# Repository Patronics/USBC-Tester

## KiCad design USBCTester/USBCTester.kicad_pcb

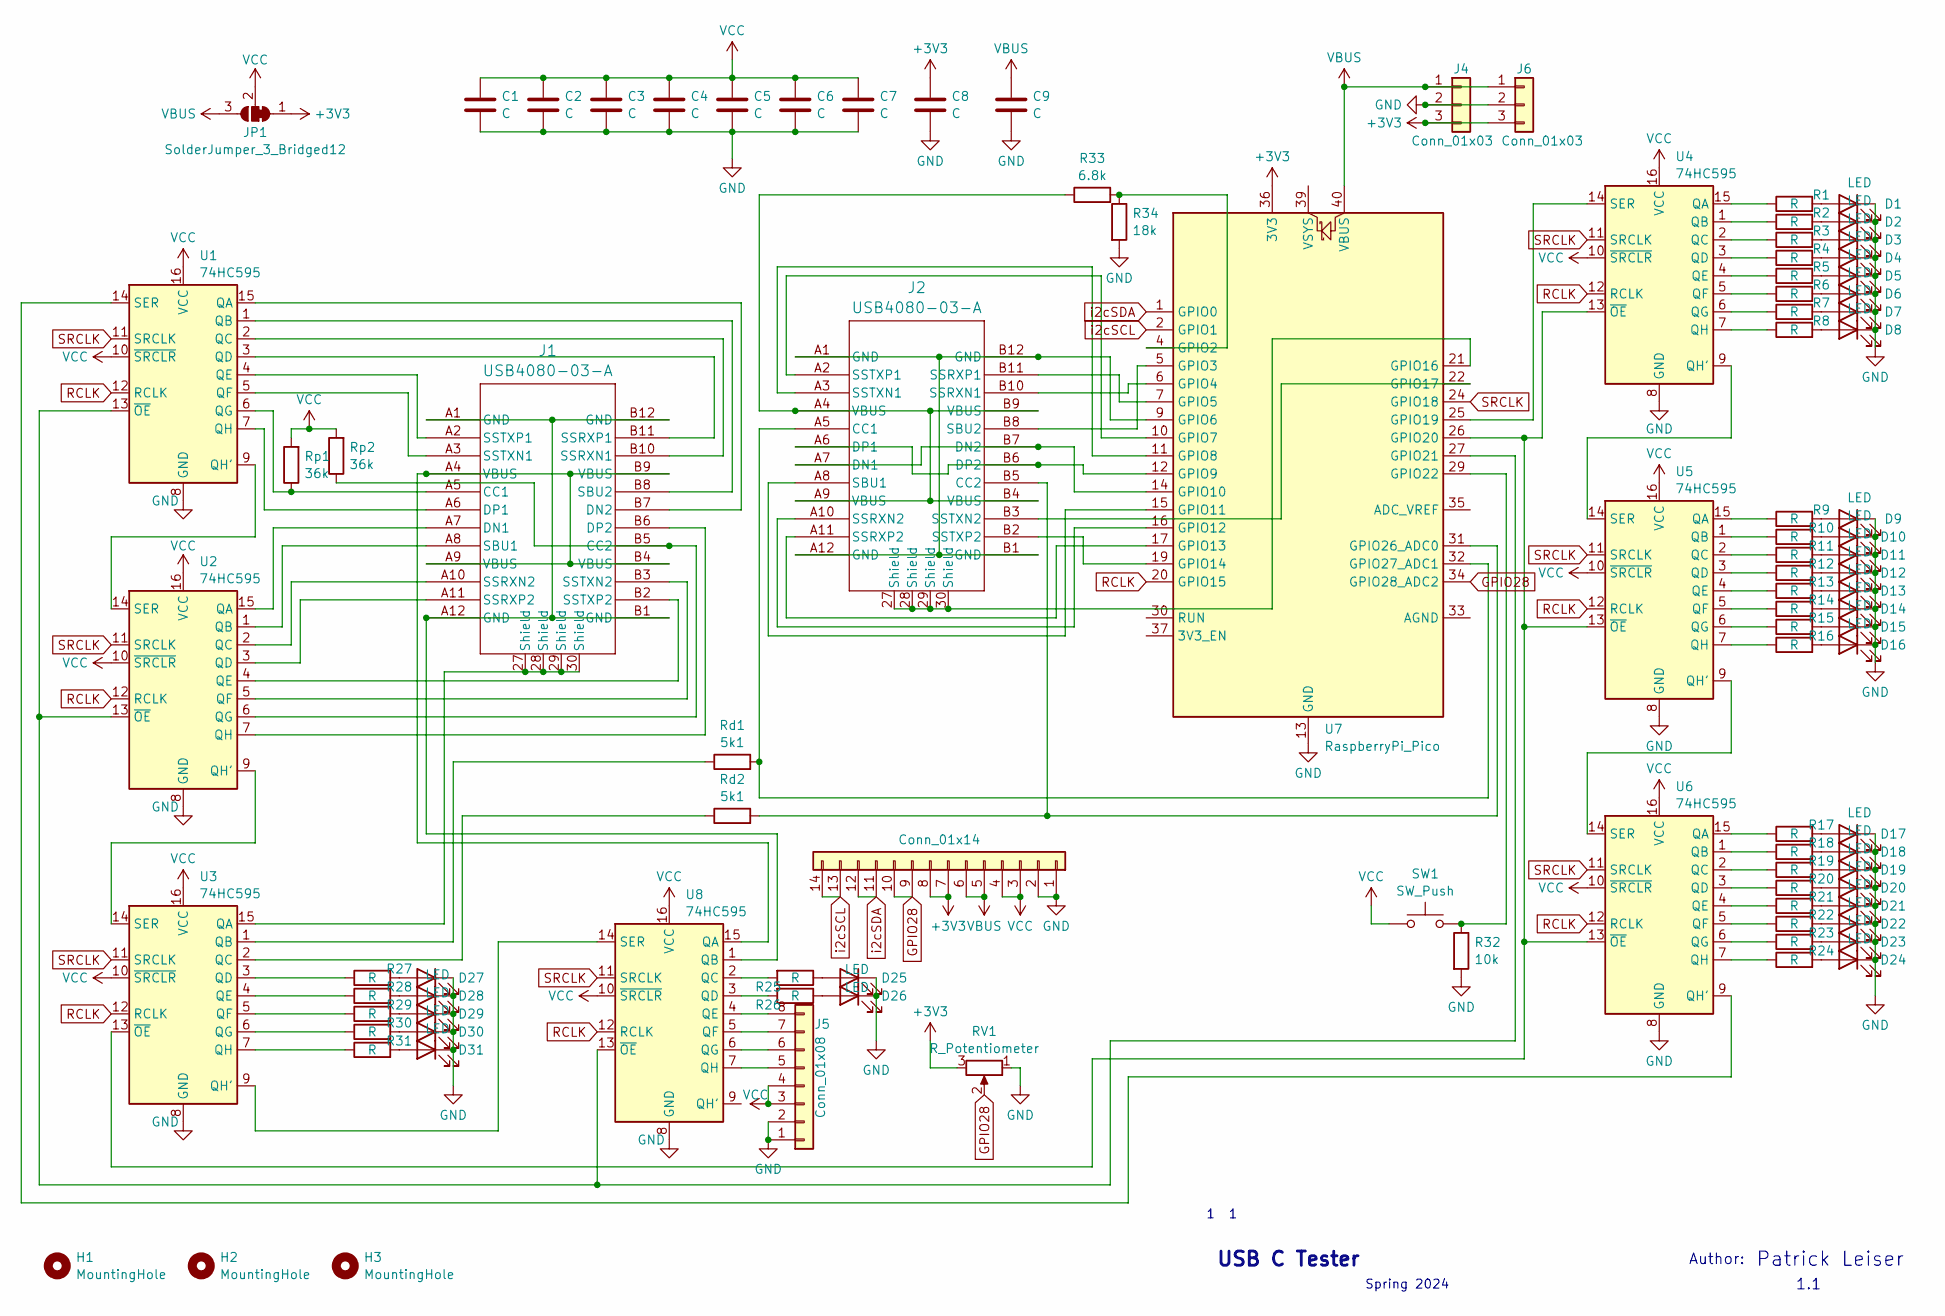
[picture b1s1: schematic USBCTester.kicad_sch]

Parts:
C1, C2, C3, C4, C5, C6, C7, C8, C9: C; C_0603_1608Metric
D1, D2, D3, D4, D5, D6, D7, D8, D9, D10, D11, D12, D13, D14, D15, D16, D17, D18, D19, D20, D21, D22, D23, D24, D25, D26, D27, D28, D29, D30, D31: LED; LED_0603_1608Metric
H1, H2, H3: MountingHole; MountingHole_3.2mm_M3
J1, J2: USB4080-03-A; USB4080-03-A_GCT_RoundHoles
J3: Conn_01x14; PinSocket_1x14_P2.54mm_Vertical
J4, J6: Conn_01x03; PinSocket_1x03_P2.54mm_Vertical
J5: Conn_01x08; PinHeader_2x04_P2.54mm_Vertical
JP1: SolderJumper_3_Bridged12; SolderJumper-3_P1.3mm_Bridged12_RoundedPad1.0x1.5mm
R1, R2, R3, R4, R5, R6, R7, R8, R9, R10, R11, R12, R13, R14, R15, R16, R17, R18, R19, R20, R21, R22, R23, R24, R25, R26, R27, R28, R29, R30, R31: R; R_0603_1608Metric
R32: 10k; R_0603_1608Metric
R33: 6.8k; R_0603_1608Metric
R34: 18k; R_0603_1608Metric
RV1: R_Potentiometer; TRIM_35WR10KLFTR
Rd1, Rd2: 5k1; R_0603_1608Metric
Rp1, Rp2: 36k; R_0603_1608Metric
SW1: SW_Push; SW_Push_1P1T_NO_6x6mm_H9.5mm
U1, U2, U3, U4, U5, U6, U8: 74HC595; SOIC-16_3.9x9.9mm_P1.27mm
U7: RaspberryPi_Pico; RaspberryPi_Pico_Common

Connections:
+3V3: C8.1, J3.7, J3.8, J4.3, J6.3, JP1.1 (A), RV1.3, U7.36 (3V3)
GND: C1.2, C2.2, C3.2, C4.2, C5.2, C6.2, C7.2, C8.2, C9.2, D1.1 (K), D2.1 (K), D3.1 (K), D4.1 (K), D5.1 (K), D6.1 (K), D7.1 (K), D8.1 (K), D9.1 (K), D10.1 (K), D11.1 (K), D12.1 (K), D13.1 (K), D14.1 (K), D15.1 (K), D16.1 (K), D17.1 (K), D18.1 (K), D19.1 (K), D20.1 (K), D21.1 (K), D22.1 (K), D23.1 (K), D24.1 (K), D25.1 (K), D26.1 (K), D27.1 (K), D28.1 (K), D29.1 (K), D30.1 (K), D31.1 (K), J3.1, J3.2, J4.2, J5.1, J5.2, J6.2, R32.2, R34.2, RV1.1, U1.8 (GND), U2.8 (GND), U3.8 (GND), U4.8 (GND), U5.8 (GND), U6.8 (GND), U7.3 (GND), U7.8 (GND), U7.13 (GND), U7.18 (GND), U7.23 (GND), U7.28 (GND), U7.38 (GND), U8.8 (GND)
GPIO28: J3.9, J3.10, RV1.2, U7.34 (GPIO28_ADC2)
unnamed: D1.2 (A), R1.2
unnamed: D2.2 (A), R2.2
unnamed: D3.2 (A), R3.2
unnamed: D4.2 (A), R4.2
unnamed: D5.2 (A), R5.2
unnamed: D6.2 (A), R6.2
unnamed: D7.2 (A), R7.2
unnamed: D8.2 (A), R8.2
unnamed: D9.2 (A), R9.2
unnamed: D10.2 (A), R10.2
unnamed: D11.2 (A), R11.2
unnamed: D12.2 (A), R12.2
unnamed: D13.2 (A), R13.2
unnamed: D14.2 (A), R14.2
unnamed: D15.2 (A), R15.2
unnamed: D16.2 (A), R16.2
unnamed: D17.2 (A), R17.2
unnamed: D18.2 (A), R18.2
unnamed: D19.2 (A), R19.2
unnamed: D20.2 (A), R20.2
unnamed: D21.2 (A), R21.2
unnamed: D22.2 (A), R22.2
unnamed: D23.2 (A), R23.2
unnamed: D24.2 (A), R24.2
unnamed: D25.2 (A), R25.1
unnamed: D26.2 (A), R26.1
unnamed: D27.2 (A), R27.2
unnamed: D28.2 (A), R28.2
unnamed: D29.2 (A), R29.2
unnamed: D30.2 (A), R30.2
unnamed: D31.2 (A), R31.2
unnamed: J1.A5 (CC1), Rp1.1, U1.6 (QG)
unnamed: J1.B5 (CC2), Rp2.1, U2.6 (QG)
unnamed: J1.A7 (DN1), U2.15 (QA)
unnamed: J1.B7 (DN2), U1.15 (QA)
unnamed: J1.A6 (DP1), U1.7 (QH)
unnamed: J1.B6 (DP2), U2.7 (QH)
unnamed: J1.A8 (SBU1), U2.1 (QB)
unnamed: J1.B8 (SBU2), U1.1 (QB)
unnamed: J1.B10 (SSRXN1), U1.2 (QC)
unnamed: J1.A10 (SSRXN2), U2.2 (QC)
unnamed: J1.B11 (SSRXP1), U1.3 (QD)
unnamed: J1.A11 (SSRXP2), U2.3 (QD)
unnamed: J1.A3 (SSTXN1), U1.5 (QF)
unnamed: J1.B3 (SSTXN2), U2.5 (QF)
unnamed: J1.A2 (SSTXP1), U1.4 (QE)
unnamed: J1.B2 (SSTXP2), U2.4 (QE)
unnamed: J2.A5 (CC1), Rd1.2, U7.32 (GPIO27_ADC1)
unnamed: J2.B5 (CC2), Rd2.2, U7.31 (GPIO26_ADC0)
unnamed: J2.A7 (DN1), J2.B7 (DN2), U7.14 (GPIO10)
unnamed: J2.A6 (DP1), J2.B6 (DP2), U7.12 (GPIO9)
unnamed: J2.A8 (SBU1), U7.15 (GPIO11)
unnamed: J2.B8 (SBU2), U7.5 (GPIO3)
unnamed: J2.B10 (SSRXN1), U7.6 (GPIO4)
unnamed: J2.A10 (SSRXN2), U7.16 (GPIO12)
unnamed: J2.B11 (SSRXP1), U7.7 (GPIO5)
unnamed: J2.A11 (SSRXP2), U7.17 (GPIO13)
unnamed: J2.A3 (SSTXN1), U7.11 (GPIO8)
unnamed: J2.B3 (SSTXN2), U7.22 (GPIO17)
unnamed: J2.A2 (SSTXP1), U7.10 (GPIO7)
unnamed: J2.B2 (SSTXP2), U7.19 (GPIO14)
unnamed: J2.A4 (VBUS), J2.A9 (VBUS), J2.B4 (VBUS), J2.B9 (VBUS), R33.1
unnamed: J5.5, U8.7 (QH)
unnamed: J5.6, U8.6 (QG)
unnamed: J5.7, U8.5 (QF)
unnamed: J5.8, U8.4 (QE)
unnamed: U1.9 (QH'), U2.14 (SER)
unnamed: U1.14 (SER), U6.9 (QH')
unnamed: U1.13 (~OE), U2.13 (~OE), U7.27 (GPIO21), U8.13 (~OE)
unnamed: U2.9 (QH'), U3.14 (SER)
unnamed: J1.27 (Shield), J1.28 (Shield), J1.29 (Shield), J1.30 (Shield), U3.15 (QA)
unnamed: Rd1.1, U3.1 (QB)
unnamed: Rd2.1, U3.2 (QC)
unnamed: R27.1, U3.3 (QD)
unnamed: R28.1, U3.4 (QE)
unnamed: R29.1, U3.5 (QF)
unnamed: R30.1, U3.6 (QG)
unnamed: U3.9 (QH'), U8.14 (SER)
unnamed: R31.1, U3.7 (QH)
unnamed: U3.13 (~OE), U4.13 (~OE), U5.13 (~OE), U6.13 (~OE), U7.26 (GPIO20)
unnamed: R1.1, U4.15 (QA)
unnamed: R2.1, U4.1 (QB)
unnamed: R3.1, U4.2 (QC)
unnamed: R4.1, U4.3 (QD)
unnamed: R5.1, U4.4 (QE)
unnamed: R6.1, U4.5 (QF)
unnamed: R7.1, U4.6 (QG)
unnamed: U4.9 (QH'), U5.14 (SER)
unnamed: R8.1, U4.7 (QH)
unnamed: U4.14 (SER), U7.25 (GPIO19)
unnamed: R9.1, U5.15 (QA)
unnamed: R10.1, U5.1 (QB)
unnamed: R11.1, U5.2 (QC)
unnamed: R12.1, U5.3 (QD)
unnamed: R13.1, U5.4 (QE)
unnamed: R14.1, U5.5 (QF)
unnamed: R15.1, U5.6 (QG)
unnamed: U5.9 (QH'), U6.14 (SER)
unnamed: R16.1, U5.7 (QH)
unnamed: R17.1, U6.15 (QA)
unnamed: R18.1, U6.1 (QB)
unnamed: R19.1, U6.2 (QC)
unnamed: R20.1, U6.3 (QD)
unnamed: R21.1, U6.4 (QE)
unnamed: R22.1, U6.5 (QF)
unnamed: R23.1, U6.6 (QG)
unnamed: R24.1, U6.7 (QH)
unnamed: R33.2, R34.1, U7.4 (GPIO2)
unnamed: J2.A1 (GND), J2.A12 (GND), J2.B1 (GND), J2.B12 (GND), U7.9 (GPIO6)
unnamed: J2.27 (Shield), J2.28 (Shield), J2.29 (Shield), J2.30 (Shield), U7.21 (GPIO16)
unnamed: R32.1, SW1.2, U7.29 (GPIO22)
unnamed: J1.A4 (VBUS), J1.A9 (VBUS), J1.B4 (VBUS), J1.B9 (VBUS), U8.15 (QA)
unnamed: J1.A1 (GND), J1.A12 (GND), J1.B1 (GND), J1.B12 (GND), U8.1 (QB)
unnamed: R25.2, U8.2 (QC)
unnamed: R26.2, U8.3 (QD)
RCLK: U1.12 (RCLK), U2.12 (RCLK), U3.12 (RCLK), U4.12 (RCLK), U5.12 (RCLK), U6.12 (RCLK), U7.20 (GPIO15), U8.12 (RCLK)
SRCLK: U1.11 (SRCLK), U2.11 (SRCLK), U3.11 (SRCLK), U4.11 (SRCLK), U5.11 (SRCLK), U6.11 (SRCLK), U7.24 (GPIO18), U8.11 (SRCLK)
VBUS: C9.1, J3.5, J3.6, J4.1, J6.1, JP1.3 (B), U7.40 (VBUS)
VCC: C1.1, C2.1, C3.1, C4.1, C5.1, C6.1, C7.1, J3.3, J3.4, J5.3, J5.4, JP1.2 (C), Rp1.2, Rp2.2, SW1.1, U1.10 (~SRCLR), U1.16 (VCC), U2.10 (~SRCLR), U2.16 (VCC), U3.10 (~SRCLR), U3.16 (VCC), U4.10 (~SRCLR), U4.16 (VCC), U5.10 (~SRCLR), U5.16 (VCC), U6.10 (~SRCLR), U6.16 (VCC), U8.10 (~SRCLR), U8.16 (VCC)
i2cSCL: J3.13, J3.14, U7.2 (GPIO1)
i2cSDA: J3.11, J3.12, U7.1 (GPIO0)

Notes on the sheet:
Author:
Spring 2024
Patrick Leiser
1.1
1 1
USB C Tester

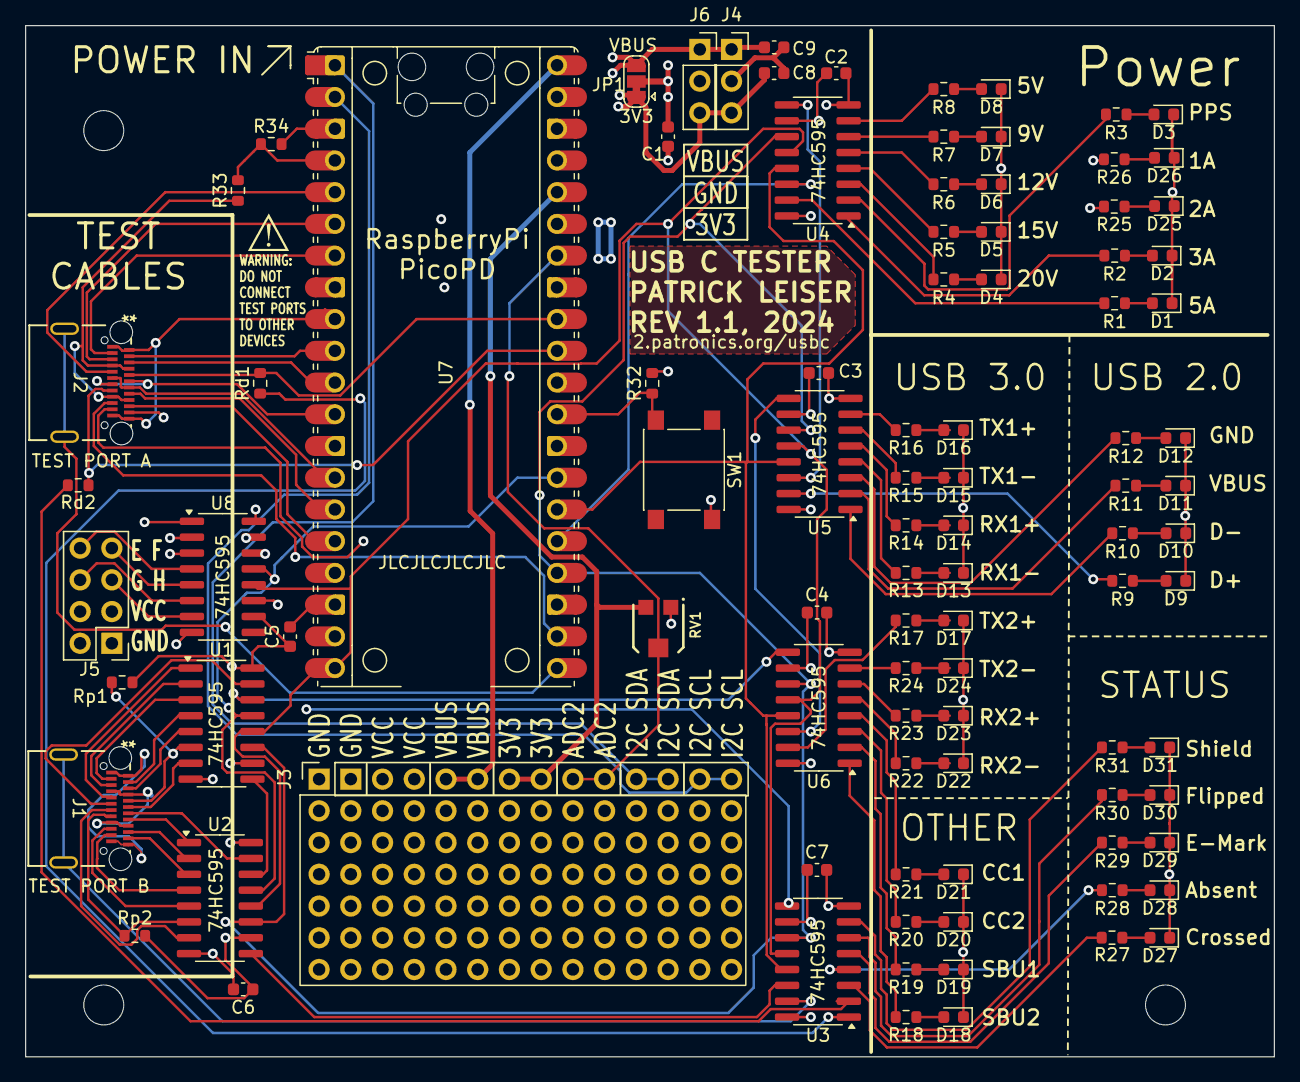
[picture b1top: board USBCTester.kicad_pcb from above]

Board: 4 copper layers, 100.0 x 82.6 mm, 99 parts (0 on the bottom side), 124 nets.

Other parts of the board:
PB1: ProtoBoard 14x6

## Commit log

2024-02-11 initial commit, add kicad files so far
2024-02-11 add power plane and vias for high current and decoupling caps
2024-02-12 continu wiring and add decoupling caps
2024-02-12 add usb c port footprint and symbol
2024-02-12 organize usb2 and usb3 status leds
2024-02-13 add more leds and route almost everything
2024-02-13 label all LEDs
2024-02-13 add breakout pins for prototyping
2024-02-16 made board more compact
2024-02-16 add 3rd incompatible footprint design
2024-02-16 switch to USB4080 footprint
2024-02-16 add protoboard, lots of tweaks and silkscreen improvements
2024-02-21 many tweaks to finalize design, then Schematic update for safety with external devices
2024-02-21 update layout with improved external device safety and testing for active cables
2024-02-26 pretty and useful back silkscreen
2024-02-27 adjust layout to preseve i2c pins, and general layout cleanup
2024-02-27 minor cleanup and reorganization
2024-02-27 adjust text background style, last 7.0 commit
2024-02-29 use older footprint for USBC since JLCPCB does seem to tolerate the shape, and minor silkscreen fixes
2024-03-04 simplify nested folders
2024-03-04 add basic openocd config file for programming via debugger
2024-03-04 move pretty footprints
2024-03-10 initial commit of power tester, proof of concept drives shift registers
2024-03-10 implemented functions for setting precice output from shift registers
2024-03-10 make remapLeds function to set LED bitmap to cleaner order
2024-03-10 minor fix and optimization
2024-03-10 successfully tests USB PD voltages
2024-03-10 animate progress in scanning supported voltages
2024-03-10 improve handling of tolerances, especially 5v tolerance
2024-03-10 rename shiftOut to shiftOutBit to avoid overriding Arduino's native shiftOut function
2024-03-11 add defines for all the pico's pins
2024-03-12 add checkPinConnection function and many #defines for pins
2024-03-12 test shield connection
2024-03-12 add software dimming of bright leds
2024-03-12 add ifdef to disable pwm dimming if not needed
2024-03-13 add errata notes
2024-03-19 update kicad files with JLC BOM and to fix silkscreen issue in V1
2024-03-19 add errata description of individual boards
2024-03-19 add #defines for each physical board made so far for hardware-specific tweaks as needed
2024-03-24 add comment noting idea for scanning brightness of power LEDs to indicate current level per supported voltage
2024-03-30 improve handling of shift registers without output enable pins
2024-03-30 add errataboard 4
2024-03-30 fine-tune timing for shift register shields
2024-03-30 WIP improve handling of shield (internally tied to ground), and start on testing other pins badly
2024-04-25 revision 1.2, add another shift register and fix the production files
2024-04-25 add resistors to db
2024-04-30 update errata to handle board rev 1.1. Final version of code optimized for v1.0 boards
2024-04-30 semi-untested modifications for rev1.1 boards
2024-04-30 fixed infinite loop due to inadequate type sizes
2024-05-01 lots of progress on getCurrentLEDsForVoltage
2024-05-03 complete getCurrentForVoltage function
2024-05-03 add tracking and displaying semantic versioning info at boot
2024-05-03 all pins defined
2024-05-03 successfully tests USB2 data+ pin
2024-05-03 testing most pins works, including D+/D-, SBU1/SBU2, and the SS pins(untested)
2024-05-03 fix handling of USB3 pins
2024-05-03 Fix power pins, shield, and re-add absent indicator
2024-05-06 add descriptive comments for CC pins
2024-05-09 slow down sampling in order to make kendrick's cable vbus work
2024-05-14 update PCB and Schematic files
2024-05-15 add draft of presentation slides
2024-05-15 finalized presentation slides
2024-05-15 add presentation handout too
2024-05-15 add source file and conversion of presentation
2024-05-15 fix background in exported powerpoint file
2024-05-15 fix inconsistient heading
2024-05-15 update PDF format and remove badly formatted powerpoint file
